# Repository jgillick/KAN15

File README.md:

# KAN-15 Switch Breakout Boards

A collection of useful PCB boards designed in KiCad for the KAN-15 push-button switch.

# LED Illumination
The best part about these switches is that they can easily be illuminated with an LED.

To do this, you need to add a spacer between the LED and the swtich. This can be a PCB spacer, or [3D printed](https://www.thingiverse.com/thing:4592896).

# Boards

* [Spacer](./Spacer) - This is just the spacer PCB. (not breadboard friendly)
* [Breakout](./Breakout) - A simple breadboard-friendly board for the swtich. It has a cavity for an LED, but no connections for one.
* [LED Stack](./LED-Stack/) - A novel 2-PCB stackup to create a thin, self-contained, LED switch.
* [RGB Stack](./RGB-Stack) - Similar to LED Stack but uses an RGB LED.

# KiCad Footprint
If you want the base KAN-15 KiCad footprint these breakout boards are based on, it is located in my general [KiCad Library](https://github.com/jgillick/KiCad-library).

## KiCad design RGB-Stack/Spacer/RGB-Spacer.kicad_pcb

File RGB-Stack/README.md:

# KAN15 RGB Stack Breakout

This stack creates a self-contained, breadboard friendly, breakout board with an RGB LED embedded under the switch. The LED will shine through the white KAN15 switch and light it up pretty well.

# PCB Stackup

* [0.8 PCB spacer](./Spacer)
* [Flex PCB bottom (for LED & resistor)](./LED)

The top PCB layer is the "spacer" creates a cavity for the [LED](https://www.digikey.com/en/products/detail/everlight-electronics-co-ltd/EAST1616RGBB2/8510360) and resistors. This should be around 0.8mm thick (or at least a little thicker than the resistor you're using).

The bottom layer has the LED and resistor and can be a thin flex PCB.

To assist with lining the layers up and holding them together, there are matching solder pads on the sides of the PCB/Flex which connect (perhaps unnecessary).

# RGB LED

The LED used for this board is a `0606 4-SMD` SMD LED (1.60mm L x 1.60mm W) with the anode on pin 4. The LED I used was [EAST1616RGBB2](https://www.digikey.com/en/products/detail/everlight-electronics-co-ltd/EAST1616RGBB2/8510360).

If you use another LED, make sure it's in a 4-pin 1.6mm square package, and matches this pin layout.

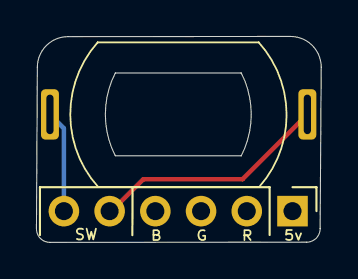
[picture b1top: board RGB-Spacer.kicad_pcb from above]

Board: 2 copper layers, 15.8 x 11.4 mm, 3 parts (1 on the bottom side), 2 nets.

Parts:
ConnPoints: Connection_Points
J1: Conn_01x06; PinHeader_1x06_P2.54mm_Vertical
SW1: KAN-15; SW_KAN-15_PHT

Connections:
/SW1: J1.5, SW1.1
/SW2: J1.6, SW1.2

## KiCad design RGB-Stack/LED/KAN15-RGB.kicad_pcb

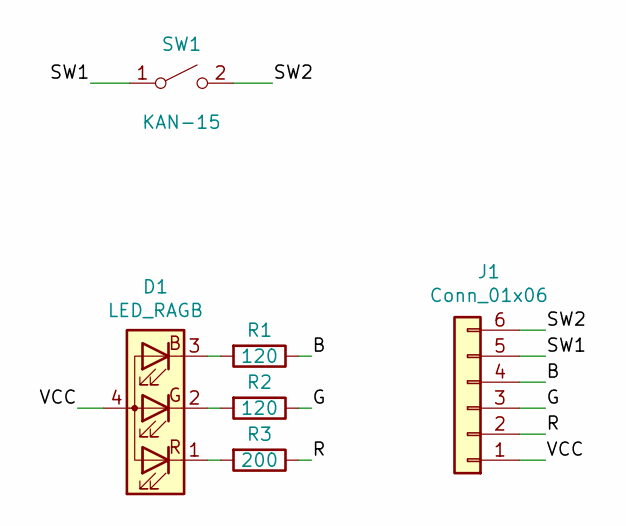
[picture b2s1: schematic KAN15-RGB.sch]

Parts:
D1: LED_RAGB; LED_RGB_0606; MPN EAST1616RGBB2; Digikey 1080-1551-1-ND
J1: Conn_01x06; PinHeader_1x06_P2.54mm_Vertical
R1, R2: 120; R_0603_1608Metric_Pad1.05x0.95mm_HandSolder
R3: 200; R_0603_1608Metric_Pad1.05x0.95mm_HandSolder
SW1: KAN-15; SW_KAN-15_PHT

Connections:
/B: J1.4, R1.1
/G: J1.3, R2.1
/R: J1.2, R3.1
/SW1: J1.5, SW1.1 (A)
/SW2: J1.6, SW1.2 (B)
/VCC: D1.4 (A), J1.1
unnamed: D1.1 (RK), R3.2
unnamed: D1.2 (GK), R2.2
unnamed: D1.3 (BK), R1.2

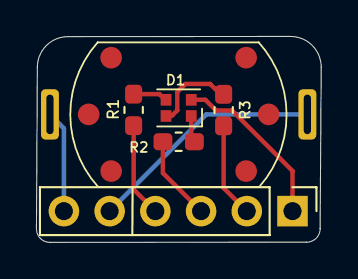
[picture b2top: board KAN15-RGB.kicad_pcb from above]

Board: 2 copper layers, 15.8 x 11.4 mm, 8 parts (1 on the bottom side), 9 nets.

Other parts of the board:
ConnPoints: Connection_Points
Ref**: Val**; switch_small

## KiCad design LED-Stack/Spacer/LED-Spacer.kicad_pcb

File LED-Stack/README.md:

# KAN15 LEDs Stack Breakout

This stack creates a self-contained, breadboard friendly, breakout board with LED. The LED will shine through the white KAN15 switch and light it up pretty well.

# PCB Stackup

* 0.8 PCB spacer
* Flex PCB bottom (for LED & resistor)

The top PCB layer is the "spacer" creates a cavity for the LED and resistor. This should be around 0.8mm thick (or at least a little thicker than the resistor you're using).

The bottom layer has the LED and resistor and can be a thin flex PCB.

To assist with lining the layers up and holding them together, there are matching solder pads on the sides of the PCB/Flex which connect (perhaps unnecessary).

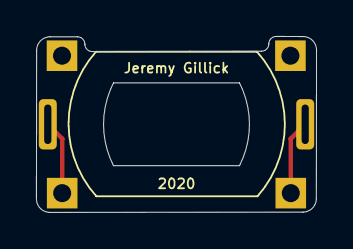
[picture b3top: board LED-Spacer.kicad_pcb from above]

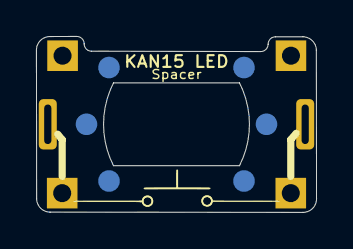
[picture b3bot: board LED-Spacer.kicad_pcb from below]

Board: 2 copper layers, 15.6 x 9.8 mm, 7 parts (2 on the bottom side), 2 nets.

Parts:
ConnPoints: Connection_Points
J1: VCC; PinHeader_1x01_P2.54mm_Vertical
J2, J3: Conn_01x01; PinHeader_1x01_P2.54mm_Vertical
J4: GND; PinHeader_1x01_P2.54mm_Vertical
Ref**: Val**; switch_large
SW1: SW_SPST; SW_KAN-15_PHT

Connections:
unnamed: J2.1, SW1.1
unnamed: J3.1, SW1.2

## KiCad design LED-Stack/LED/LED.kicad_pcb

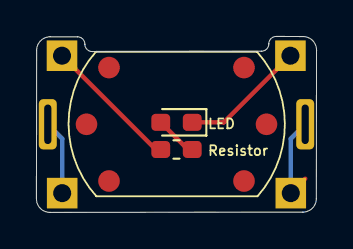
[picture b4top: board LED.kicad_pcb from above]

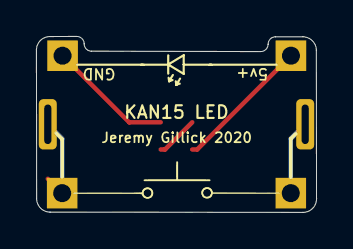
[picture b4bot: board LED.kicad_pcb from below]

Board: 2 copper layers, 15.6 x 9.8 mm, 10 parts (2 on the bottom side), 5 nets.

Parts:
ConnPoints: Connection_Points
J1: VCC; PinHeader_1x01_P2.54mm_Vertical
J2, J3: Conn_01x01; PinHeader_1x01_P2.54mm_Vertical
J4: GND; PinHeader_1x01_P2.54mm_Vertical
LED: LED; LED_0603_1608Metric_Pad1.05x0.95mm_HandSolder
LED Symbol: Val**; LED_symbol
Ref**: Val**; switch_large
Resistor: 200; R_0603_1608Metric_Pad1.05x0.95mm_HandSolder
SW1: SW_SPST; SW_KAN-15_PHT

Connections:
unnamed: J4.1, LED.1
unnamed: LED.2, Resistor.1
unnamed: J1.1, Resistor.2
unnamed: J2.1, SW1.1
unnamed: J3.1, SW1.2

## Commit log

2020-10-09 Add breakout and LED stack.
2020-10-12 Update LED stack 3D renderings.
2020-10-12 More docs.
2020-10-12 Add RGB LED breakout board.
2020-10-12 Link layers.
